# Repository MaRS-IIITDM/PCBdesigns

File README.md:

# PCBdesigns
This repository contains the `.sch` and `.brd` files of the PCBs used in the rover. All `.step` files of the used modules and componenets in the design are also present in the following folder  `[design name]/step_files`.

## Folling are the designed PCBs as of now

### Rover's power supply:

### Rover's steering controller:

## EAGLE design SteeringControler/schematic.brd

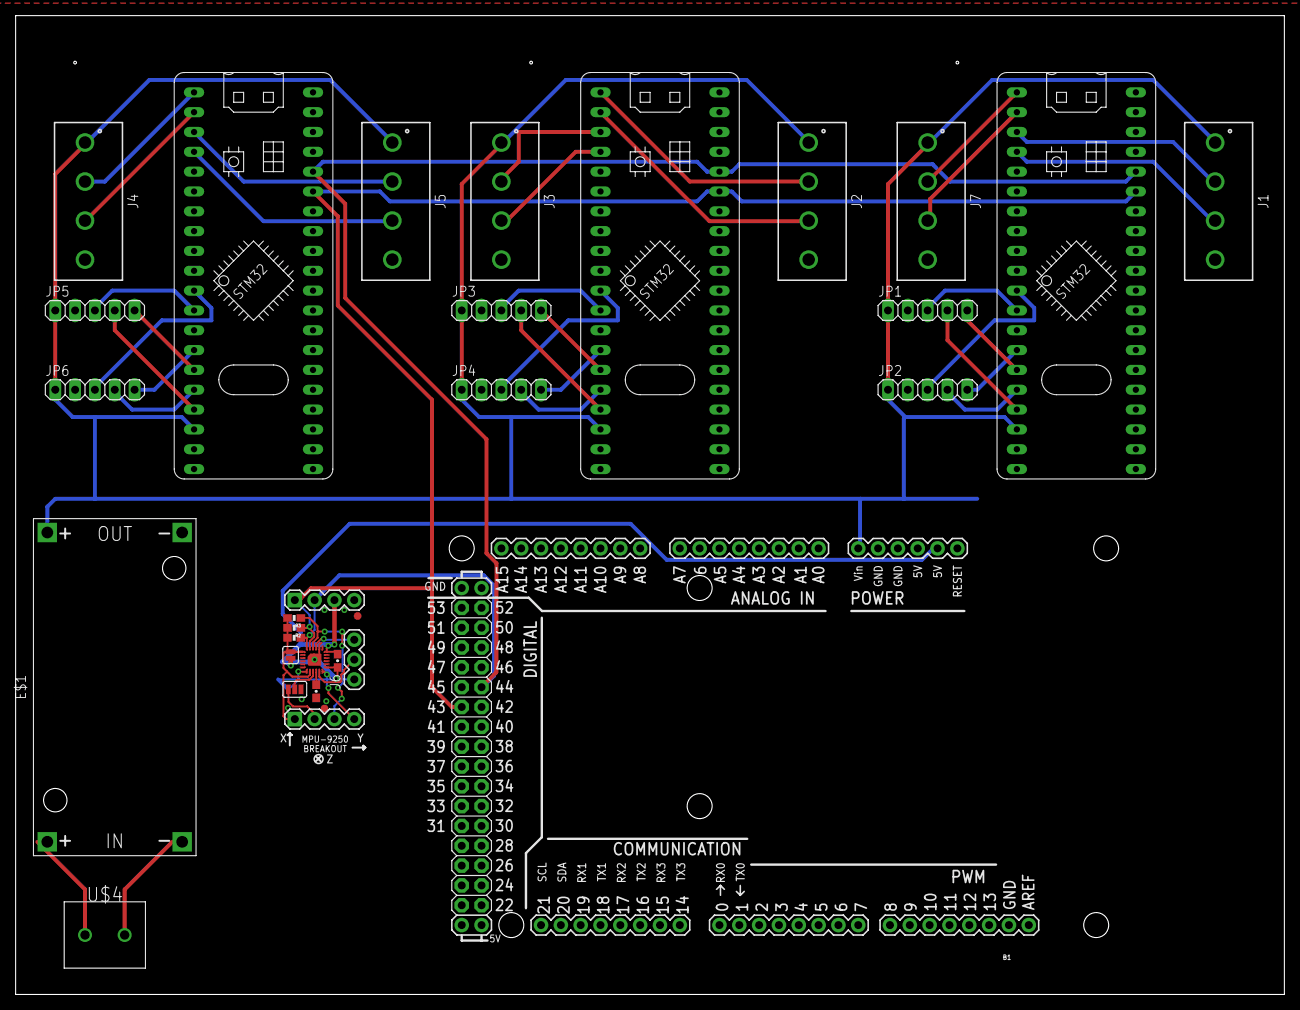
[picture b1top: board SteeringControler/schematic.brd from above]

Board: 2 copper layers, 162.5 x 125.4 mm, 31 parts (0 on the bottom side), 44 nets.

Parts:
B1: ARDUINO_MEGA_R3FULL; ARDUINO_MEGA
C1, C2: 0.1uF; 0603-CAP
E$1: DC-DC-STEP-DOWN-LM2596
FID1, FID2: FIDUCIAL1X2; FIDUCIAL-1X2
J1, J2, J3, J4, J5, J7: 691311700004
J6: 1X03
J8, J9: 1X04
JP1, JP2, JP3, JP4, JP5, JP6: PINHD-1X5; 1X05
R1, R2, R3: 10K; 0603-RES
SJ1: JUMPER-PAD-2-NC_BY_PASTEFULL-BOX-SILK; PAD-JUMPER-2-NC_BY_PASTE_YES_SILK_FULL_BOX
SJ2: JUMPER_PAD-3-1&2_NC_BY_PASTE; PAD-HUMPER-3-1&2_NC_BY_PASTE_YES_SILK_FULL_BOX
U1: MPU-9250; QFN24_PAD
U$1, U$2, U$3: BLUE_PILL
U$4: 2828XX-2282837-2; TERMBLK_508-2N

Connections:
!CS: J9.3, R3.1, U1.22
AD0/SDO: J9.2, SJ2.3
ADSD_STUB: SJ2.2, U1.9
AUX_CL: J6.1, U1.7
AUX_DA: J6.3, U1.21
FSYNC: J6.2, U1.11
GND: B1.GND@3, B1.GND@4, C1.2, C2.2, E$1.OUT-, J1.4, J2.4, J3.4, J4.4, J5.4, J7.4, J8.4, JP1.2, JP2.2, JP3.2, JP4.2, JP5.2, JP6.2, SJ2.1, U1.18, U1.20, U1.CENTER, U$1.P$19, U$1.P$21, U$2.P$19, U$2.P$21, U$3.P$19, U$3.P$21
INT: J9.4, U1.12
unnamed: J7.2, U$1.P$1
unnamed: J7.3, U$1.P$2
unnamed: J1.2, U$1.P$3
unnamed: J1.3, U$1.P$4
unnamed: J2.2, U$2.P$1
unnamed: J2.3, U$2.P$2
unnamed: J3.2, U$2.P$3
unnamed: J3.3, U$2.P$4
unnamed: JP2.5, U$1.P$14
unnamed: JP1.5, U$1.P$15
unnamed: JP2.4, U$1.P$16
unnamed: JP1.4, U$1.P$17
unnamed: JP2.3, U$1.P$11
unnamed: JP1.3, U$1.P$12
unnamed: JP4.5, U$2.P$14
unnamed: JP3.5, U$2.P$15
unnamed: JP4.4, U$2.P$16
unnamed: JP3.4, U$2.P$17
unnamed: JP4.3, U$2.P$11
unnamed: JP3.3, U$2.P$12
unnamed: J4.2, U$3.P$1
unnamed: J4.3, U$3.P$2
unnamed: J5.2, U$3.P$3
unnamed: J5.3, U$3.P$4
unnamed: JP6.5, U$3.P$14
unnamed: JP5.5, U$3.P$15
unnamed: JP6.4, U$3.P$16
unnamed: JP5.4, U$3.P$17
unnamed: JP6.3, U$3.P$11
unnamed: JP5.3, U$3.P$12
REGOUT: C1.1, U1.10
S$2: B1.3.3V, C2.1, J8.3, SJ1.1, U1.13
SCL/SCLK: B1.43, J8.1, R2.1, U1.23, U$1.P$26, U$2.P$26, U$3.P$26
SDA/SDI: B1.44, J8.2, R1.1, U1.24, U$1.P$25, U$2.P$25, U$3.P$25
VDD: B1.VIN, E$1.OUT+, J1.1, J2.1, J3.1, J4.1, J5.1, J7.1, JP1.1, JP2.1, JP3.1, JP4.1, JP5.1, JP6.1, U$1.P$18, U$2.P$18, U$3.P$18
VDDIO: J9.1, R1.2, R2.2, R3.2, SJ1.2, U1.1, U1.8

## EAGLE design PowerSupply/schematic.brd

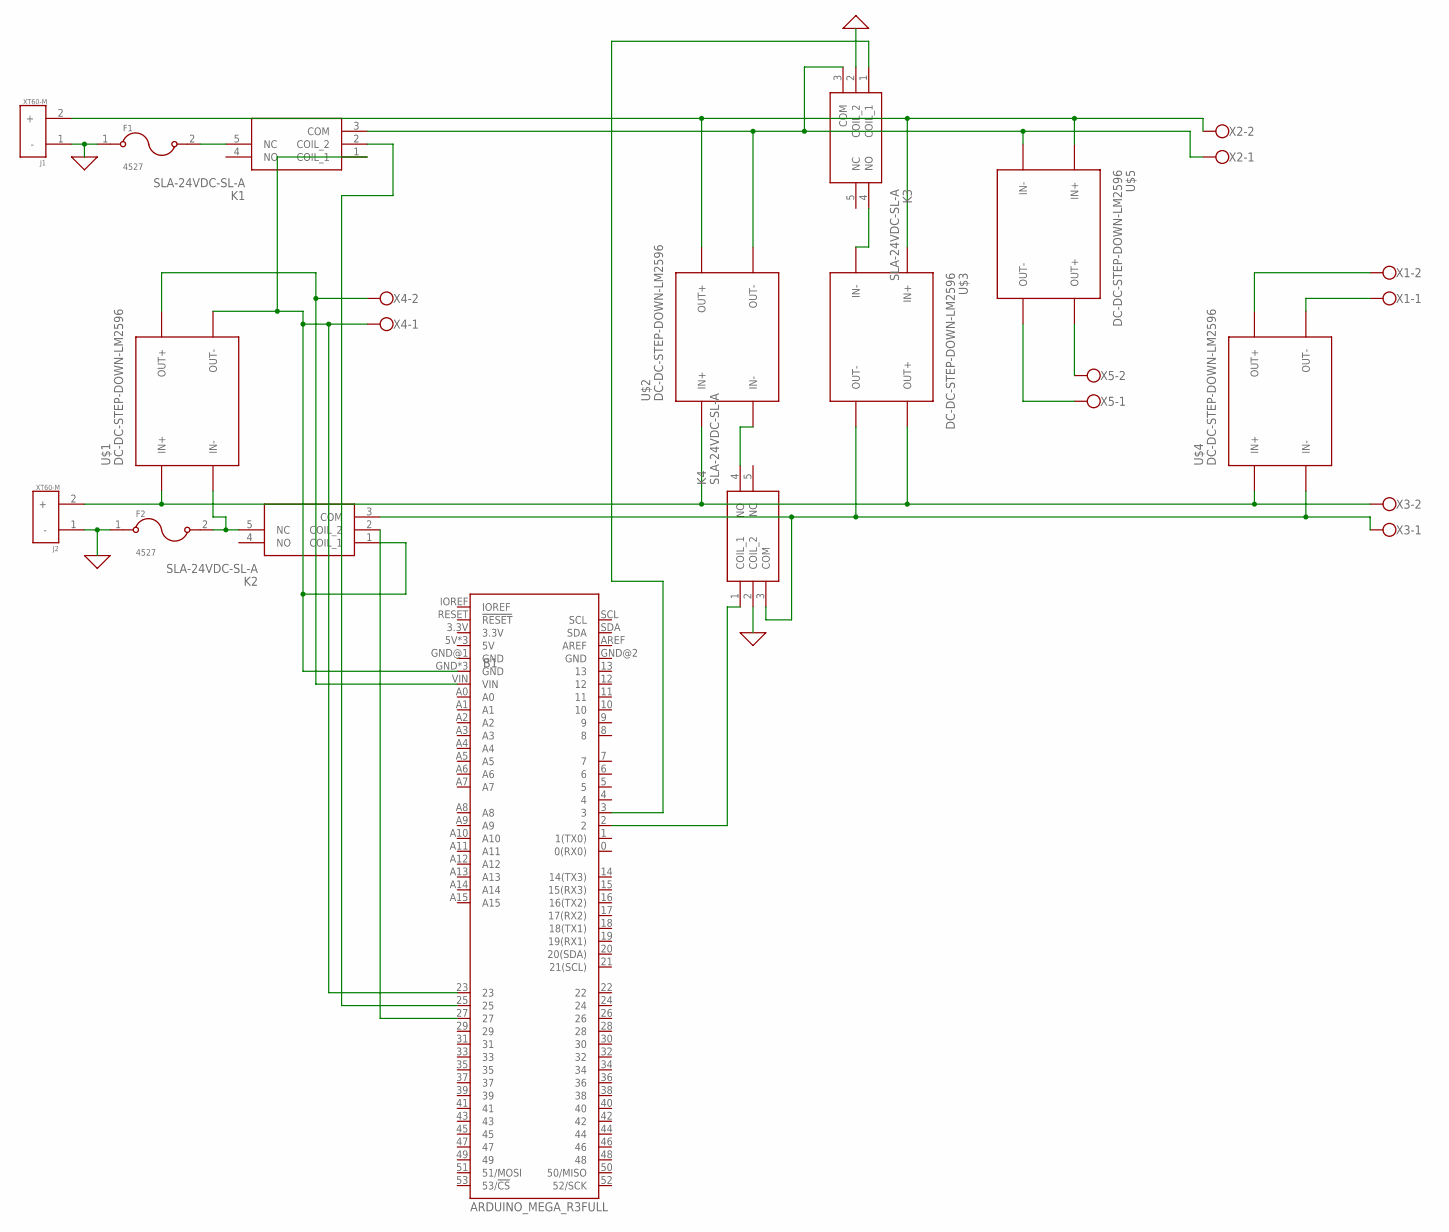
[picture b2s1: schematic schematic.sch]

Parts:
B1: ARDUINO_MEGA_R3FULL; ARDUINO_MEGA_NO_SILK
F1, F2: 4527; FUSE_4527
J1, J2: XT60-M; AMASS_XT60-M
K1, K2, K3, K4: SLA-24VDC-SL-A; SLA24VDCSLA
U$1, U$2, U$3, U$4, U$5: DC-DC-STEP-DOWN-LM2596
X1, X2, X3, X4, X5: W237-102

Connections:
0: F1.1, F2.1, J1.1 (-), J2.1 (-), K3.2 (COIL_2), K4.2 (COIL_2)
unnamed: J1.2 (+), U$2.OUT+, U$3.IN+, U$5.IN+, X2.2
unnamed: F1.2, K1.5 (NC)
unnamed: K1.3 (COM), K3.3 (COM), U$2.OUT-, U$5.IN-, X2.1
unnamed: F2.2, K2.5 (NC), U$1.IN-
unnamed: J2.2 (+), U$1.IN+, U$2.IN+, U$3.OUT+, U$4.IN+, X3.2
unnamed: K2.3 (COM), K4.3 (COM), U$3.OUT-, U$4.IN-, X3.1
unnamed: B1.27, K2.2 (COIL_2)
unnamed: B1.VIN, U$1.OUT+, X4.2
unnamed: B1.23, B1.GND, B1.GND@3 (GND), B1.GND@4 (GND), K1.1 (COIL_1), K2.1 (COIL_1), U$1.OUT-, X4.1
unnamed: U$5.OUT+, X5.2
unnamed: B1.25, K1.2 (COIL_2)
unnamed: U$5.OUT-, X5.1
unnamed: U$4.OUT+, X1.2
unnamed: U$4.OUT-, X1.1
unnamed: K3.4 (NO), U$3.IN-
unnamed: K4.4 (NO), U$2.IN-
unnamed: B1.2, K4.1 (COIL_1)
unnamed: B1.3, K3.1 (COIL_1)

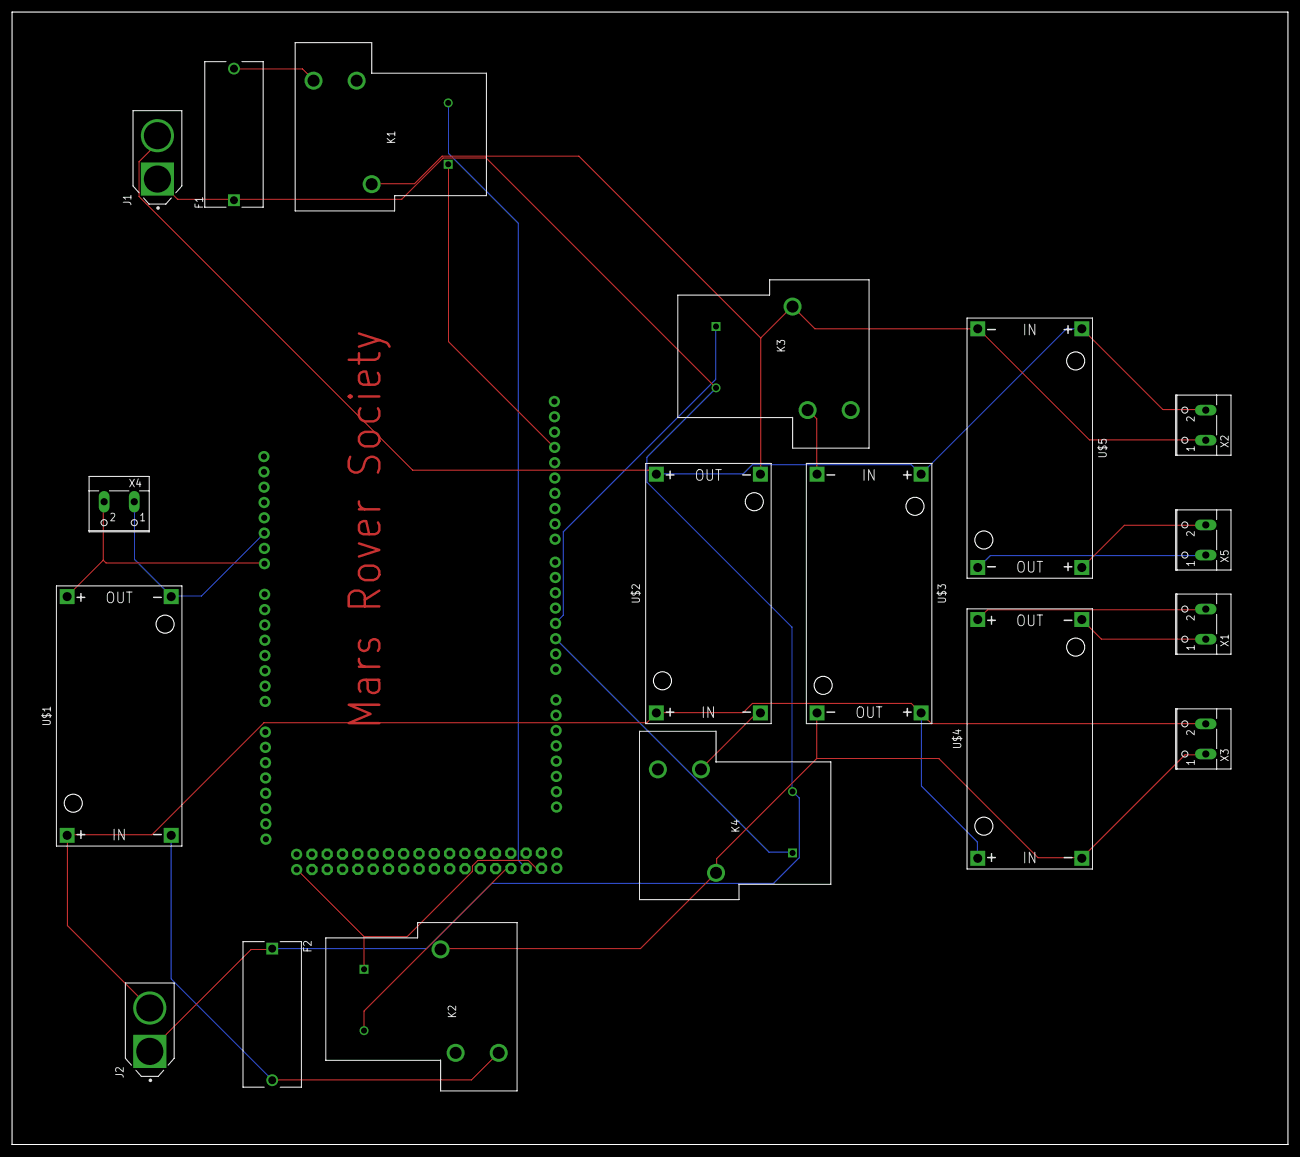
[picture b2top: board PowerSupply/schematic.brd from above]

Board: 2 copper layers, 211.8 x 187.9 mm, 19 parts (0 on the bottom side), 19 nets.

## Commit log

2021-06-12 power supply project is uploaded
    all schematics and board files of the project are uploaded.
2021-06-12 readme file updated
2021-06-12 pics of the designs are uploaded.
2021-06-12 updated readme file
    added pictures
2021-06-12 uploaded step files
2021-06-13 steering controller PCB designs are uploaded
    all the schematics, bird files and pics of the PCB design are uploaded
2021-06-13 updated readme file
    updated readme.md file with steering controller PCB pics

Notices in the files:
parts and their libraries:
SparkFun-Boards: Licensing: Creative Commons ShareAlike 4.0 International - https://creativecommons.org/licenses/by-sa/4.0
diy-modules: Released under the Creative Commons Attribution 4.0 International License: http://creativecommons.org/licenses/by/4.0
